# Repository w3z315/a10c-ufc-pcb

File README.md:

> [!CAUTION]
> This repository has moved to [https://github.com/w3z315/a10c-simpit-pcbs](https://github.com/w3z315/a10c-simpit-pcbs) because I migrated to a single repository that is a collection of all my PCBs and Arduino code.

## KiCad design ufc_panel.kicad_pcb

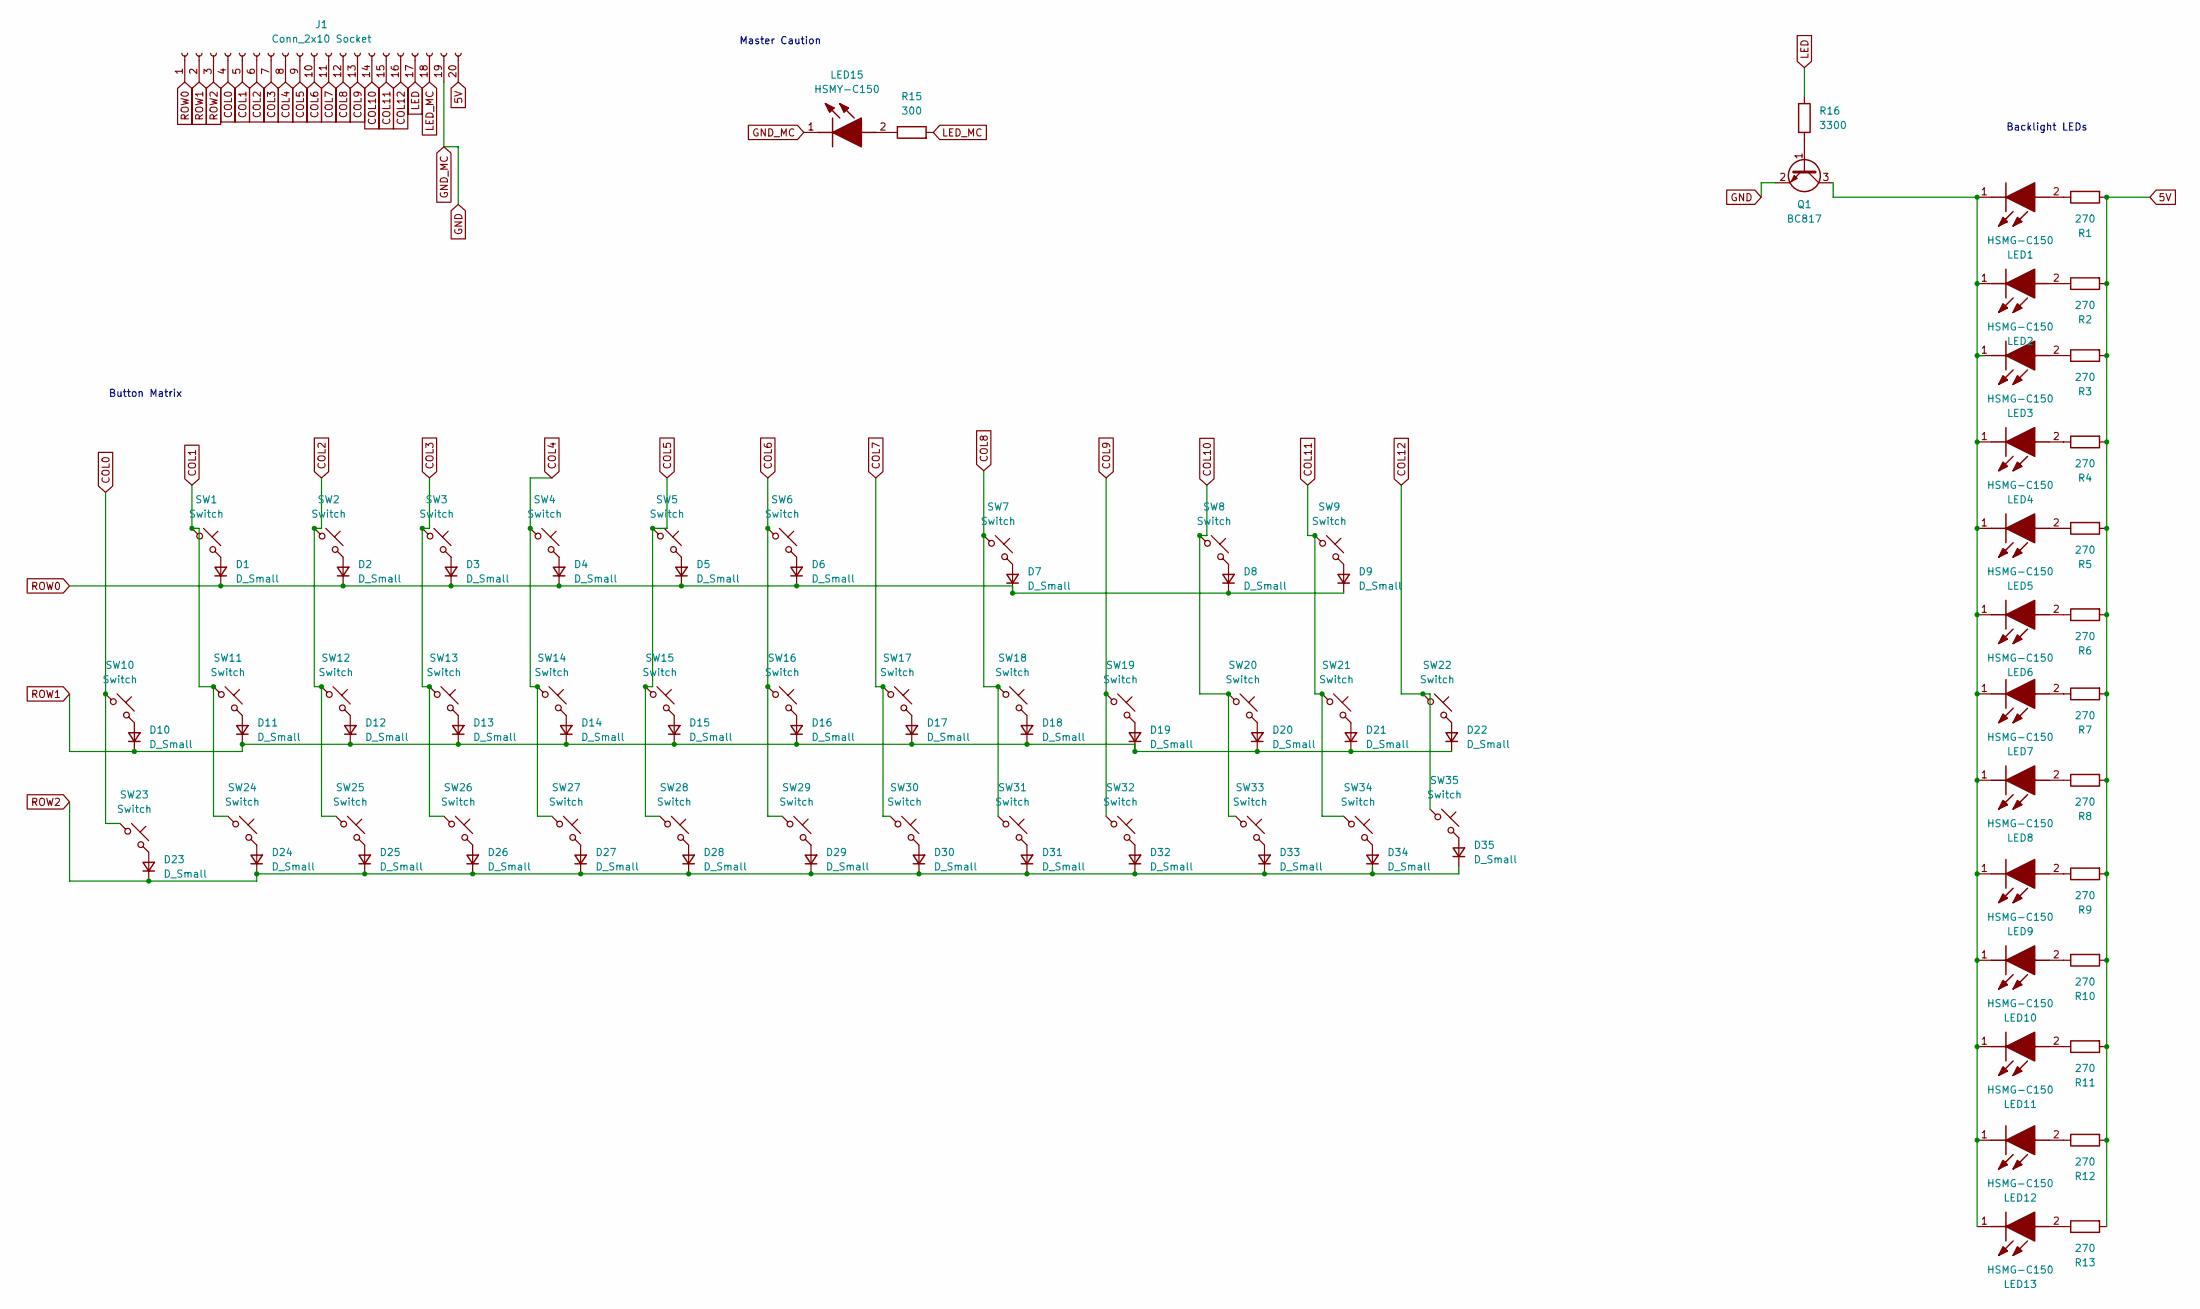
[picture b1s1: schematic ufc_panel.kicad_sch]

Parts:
D1, D2, D3, D4, D5, D6, D7, D8, D9, D10, D11, D12, D13, D14, D15, D16, D17, D18, D19, D20, D21, D22, D23, D24, D25, D26, D27, D28, D29, D30, D31, D32, D33, D34, D35: D_Small; D_SOD-123
J1: Conn_2x10 Socket; PinHeader_1x20_P2.54mm_Vertical
LED1, LED2, LED3, LED4, LED5, LED6, LED7, LED8, LED9, LED10, LED11, LED12, LED13: HSMG-C150; LED_1206_3216Metric_Pad1.42x1.75mm_HandSolder; Mouser Part Number 630-HSMG-C150
LED15: HSMY-C150; LED_1206_3216Metric_Pad1.42x1.75mm_HandSolder; Mouser Part Number 630-HSMY-C150
Q1: BC817; SOT-23
R1, R2, R3, R4, R5, R6, R7, R8, R9, R10, R11, R12, R13: 270; R_1206_3216Metric
R15: 300; R_1206_3216Metric
R16: 3300; R_0603_1608Metric
SW1, SW2, SW3, SW4, SW5, SW6, SW7, SW8, SW9, SW10, SW11, SW12, SW13, SW14, SW15, SW16, SW17, SW18, SW19, SW20, SW21, SW22, SW23, SW24, SW25, SW26, SW27, SW28, SW29, SW30, SW31, SW32, SW33, SW34, SW35: Switch; SW_PUSH_6mm_H4.3mm_INT_CONNECTED

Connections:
5V: J1.20, R1.2, R2.2, R3.2, R4.2, R5.2, R6.2, R7.2, R8.2, R9.2, R10.2, R11.2, R12.2, R13.2
COL0: J1.4, SW10.1, SW23.1
COL1: J1.5, SW1.1, SW11.1, SW24.1
COL2: J1.6, SW2.1, SW12.1, SW25.1
COL3: J1.7, SW3.1, SW13.1, SW26.1
COL4: J1.8, SW4.1, SW14.1, SW27.1
COL5: J1.9, SW5.1, SW15.1, SW28.1
COL6: J1.10, SW6.1, SW16.1, SW29.1
COL7: J1.11, SW17.1, SW30.1
COL8: J1.12, SW7.1, SW18.1, SW31.1
COL9: J1.13, SW19.1, SW32.1
COL10: J1.14, SW8.1, SW20.1, SW33.1
COL11: J1.15, SW9.1, SW21.1, SW34.1
COL12: J1.16, SW22.1, SW35.1
GND: J1.19, LED15.1 (K), Q1.2 (E)
LED: J1.17, R16.1
LED_MC: J1.18, R15.2
unnamed: D1.2 (A), SW1.2
unnamed: D2.2 (A), SW2.2
unnamed: D3.2 (A), SW3.2
unnamed: D4.2 (A), SW4.2
unnamed: D5.2 (A), SW5.2
unnamed: D6.2 (A), SW6.2
unnamed: D7.2 (A), SW7.2
unnamed: D8.2 (A), SW8.2
unnamed: D9.2 (A), SW9.2
unnamed: D10.2 (A), SW10.2
unnamed: D11.2 (A), SW11.2
unnamed: D12.2 (A), SW12.2
unnamed: D13.2 (A), SW13.2
unnamed: D14.2 (A), SW14.2
unnamed: D15.2 (A), SW15.2
unnamed: D16.2 (A), SW16.2
unnamed: D17.2 (A), SW17.2
unnamed: D18.2 (A), SW18.2
unnamed: D19.2 (A), SW19.2
unnamed: D20.2 (A), SW20.2
unnamed: D21.2 (A), SW21.2
unnamed: D22.2 (A), SW22.2
unnamed: D23.2 (A), SW23.2
unnamed: D24.2 (A), SW24.2
unnamed: D25.2 (A), SW25.2
unnamed: D26.2 (A), SW26.2
unnamed: D27.2 (A), SW27.2
unnamed: D28.2 (A), SW28.2
unnamed: D29.2 (A), SW29.2
unnamed: D30.2 (A), SW30.2
unnamed: D31.2 (A), SW31.2
unnamed: D32.2 (A), SW32.2
unnamed: D33.2 (A), SW33.2
unnamed: D34.2 (A), SW34.2
unnamed: D35.2 (A), SW35.2
unnamed: LED1.2 (A), R1.1
unnamed: LED1.1 (K), LED2.1 (K), LED3.1 (K), LED4.1 (K), LED5.1 (K), LED6.1 (K), LED7.1 (K), LED8.1 (K), LED9.1 (K), LED10.1 (K), LED11.1 (K), LED12.1 (K), LED13.1 (K), Q1.3 (C)
unnamed: LED2.2 (A), R2.1
unnamed: LED3.2 (A), R3.1
unnamed: LED4.2 (A), R4.1
unnamed: LED5.2 (A), R5.1
unnamed: LED6.2 (A), R6.1
unnamed: LED7.2 (A), R7.1
unnamed: LED8.2 (A), R8.1
unnamed: LED9.2 (A), R9.1
unnamed: LED10.2 (A), R10.1
unnamed: LED11.2 (A), R11.1
unnamed: LED12.2 (A), R12.1
unnamed: LED13.2 (A), R13.1
unnamed: LED15.2 (A), R15.1
unnamed: Q1.1 (B), R16.2
ROW0: D1.1 (K), D2.1 (K), D3.1 (K), D4.1 (K), D5.1 (K), D6.1 (K), D7.1 (K), D8.1 (K), D9.1 (K), J1.1
ROW1: D10.1 (K), D11.1 (K), D12.1 (K), D13.1 (K), D14.1 (K), D15.1 (K), D16.1 (K), D17.1 (K), D18.1 (K), D19.1 (K), D20.1 (K), D21.1 (K), D22.1 (K), J1.2
ROW2: D23.1 (K), D24.1 (K), D25.1 (K), D26.1 (K), D27.1 (K), D28.1 (K), D29.1 (K), D30.1 (K), D31.1 (K), D32.1 (K), D33.1 (K), D34.1 (K), D35.1 (K), J1.3

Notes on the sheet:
Button Matrix
Backlight LEDs
Master Caution

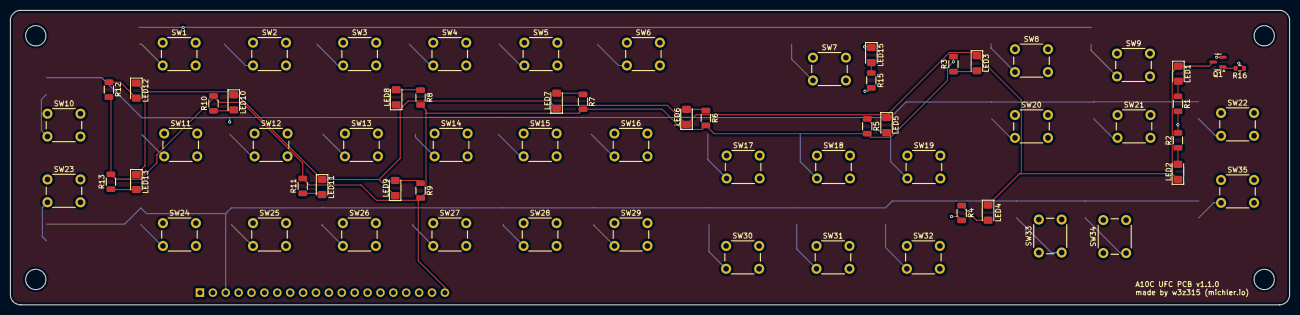
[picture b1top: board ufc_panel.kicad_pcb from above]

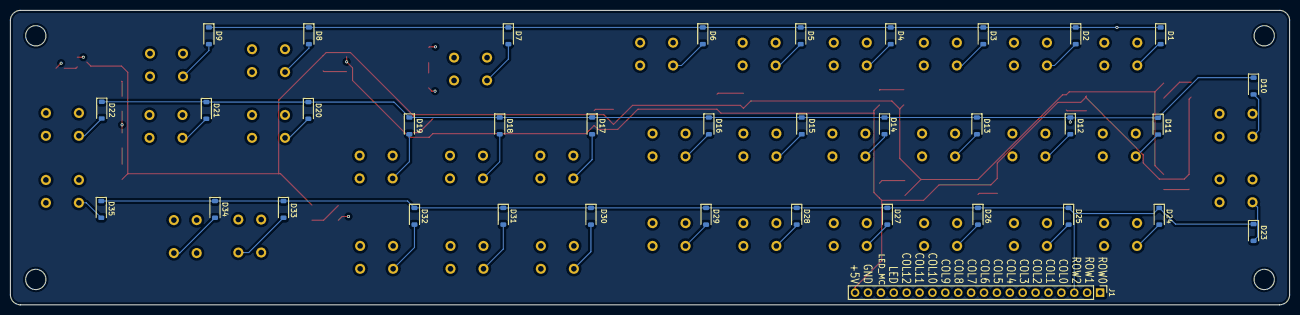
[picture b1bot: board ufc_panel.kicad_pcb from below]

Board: 4 copper layers, 252.0 x 58.0 mm, 101 parts (36 on the bottom side), 71 nets.

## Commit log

2024-03-09 feat: initial commit of ufc prototype
2024-03-09 chore: add license
2024-03-09 fix: wrong license link in readme
2024-03-09 fix: wrong link in readme to blog
2024-03-10 feat: new version - v1.1; redesigned traces, connector, etc
2024-03-12 feat: now using 4 layer pcb
2024-03-21 chore: added more images, sponsorship note
2024-05-23 chore: modify readme
2024-05-23 chore: update readme
2024-05-27 chore: archive repository, add readme for new repo url
